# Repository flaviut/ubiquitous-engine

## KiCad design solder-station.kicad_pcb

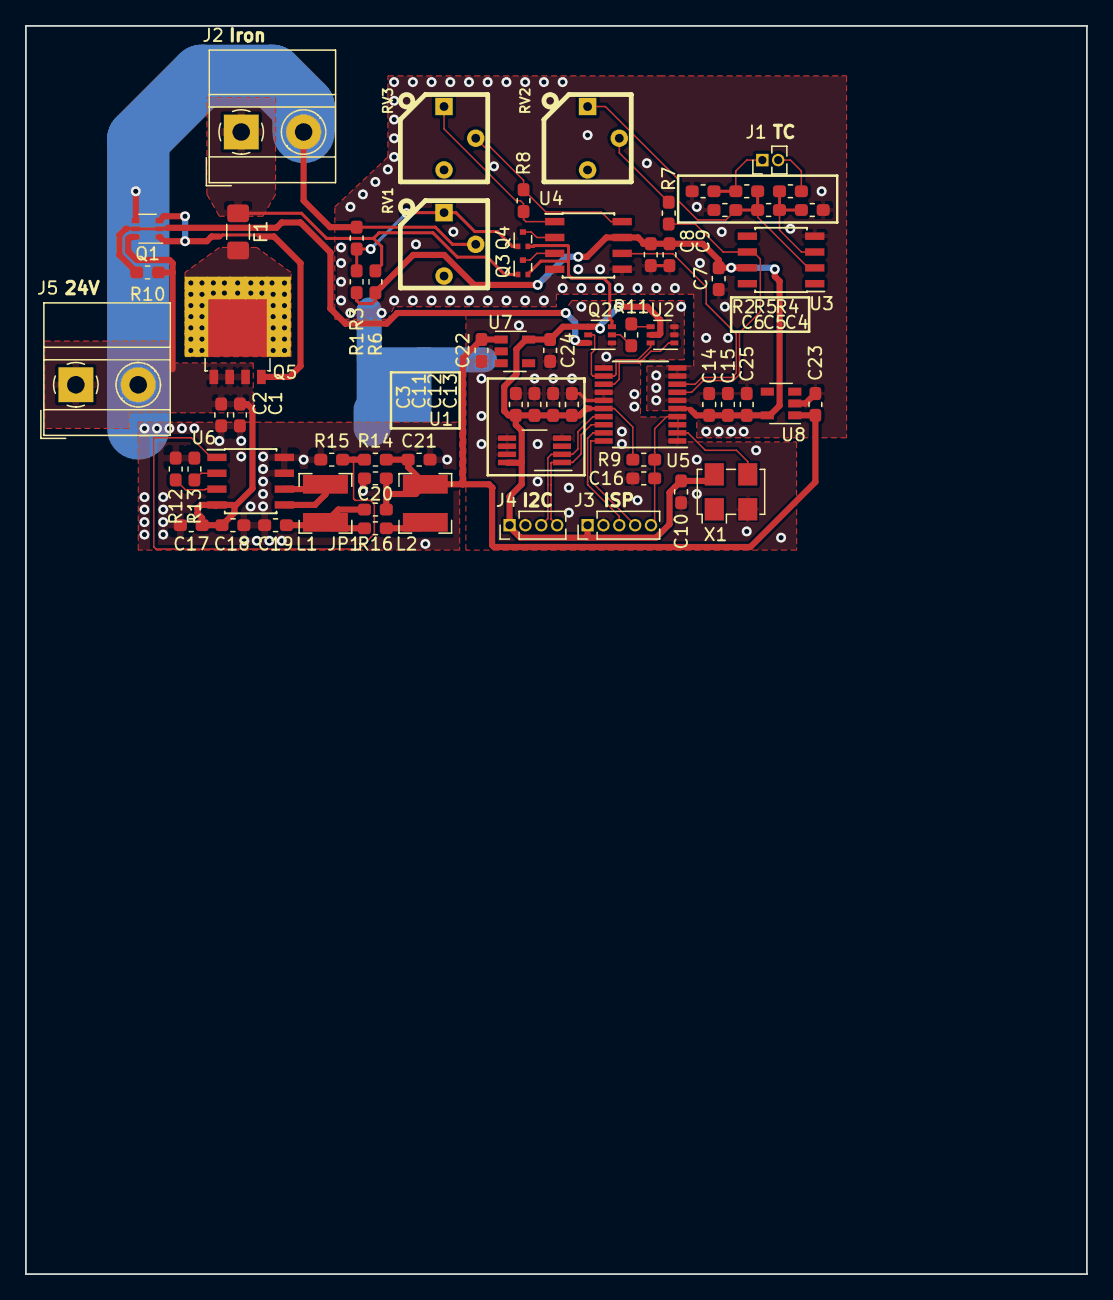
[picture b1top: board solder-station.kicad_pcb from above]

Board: 2 copper layers, 85.0 x 100.0 mm, 68 parts (1 on the bottom side), 40 nets.

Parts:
C1, C10, C11: 4.7u; C_0603_1608Metric_Pad1.05x0.95mm_HandSolder
C2, C7, C8, C12, C13, C14, C16: .1u; C_0603_1608Metric_Pad1.05x0.95mm_HandSolder
C3, C9, C15, C22, C23, C24, C25: 1u; C_0603_1608Metric_Pad1.05x0.95mm_HandSolder
C4, C6: 1n; C_0603_1608Metric_Pad1.05x0.95mm_HandSolder
C5: 10n; C_0603_1608Metric_Pad1.05x0.95mm_HandSolder
C17, C18, C19, C20, C21: 47u; C_0603_1608Metric_Pad1.05x0.95mm_HandSolder
F1: 10A; Fuse_1206_3216Metric_Pad1.42x1.75mm_HandSolder
J1: Temp Sensor; PinHeader_1x02_P1.27mm_Vertical
J2: Heating Element; TerminalBlock_MetzConnect_Type011_RT05502HBWC_1x02_P5.00mm_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
J3: ISP; PinHeader_1x05_P1.27mm_Vertical
J4: I2C; PinHeader_1x04_P1.27mm_Vertical
J5: Power; TerminalBlock_MetzConnect_Type011_RT05502HBWC_1x02_P5.00mm_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
JP1: SolderJumper_2_Open; R_0603_1608Metric_Pad1.05x0.95mm_HandSolder
L1, L2: 4.7u; L_Bourns-SRN4018
NT1: Star Ground; NetTie-4_SMD_Pad2.0mm
Q1, Q2: MBT3946DW1T1; SOT-363_SC-70-6
Q3, Q4: L2N7002M3T5G; SOT-723
Q5: FDMS6681Z; LFPAK56_ThermalVias-1
R1, R6: 2k 0.1%; R_0603_1608Metric_Pad1.05x0.95mm_HandSolder
R2, R7: 1M; R_0603_1608Metric_Pad1.05x0.95mm_HandSolder
R3: 3.3; R_0603_1608Metric_Pad1.05x0.95mm_HandSolder
R4, R5, R10: 10k; R_0603_1608Metric_Pad1.05x0.95mm_HandSolder
R8: DNP; R_0603_1608Metric_Pad1.05x0.95mm_HandSolder
R9: 100k; R_0603_1608Metric_Pad1.05x0.95mm_HandSolder
R11: 0; R_0603_1608Metric_Pad1.05x0.95mm_HandSolder
R12: 27k; R_0603_1608Metric_Pad1.05x0.95mm_HandSolder
R13: 120k; R_0603_1608Metric_Pad1.05x0.95mm_HandSolder
R14: 475k; R_0603_1608Metric_Pad1.05x0.95mm_HandSolder
R15: 150k; R_0603_1608Metric_Pad1.05x0.95mm_HandSolder
R16: 150m; R_0603_1608Metric_Pad1.05x0.95mm_HandSolder
RV1: 3362P-1-100; BOURNS-3362P_pot
RV2: 3362P-1-105; BOURNS-3362P_pot
RV3: 3362P-1-502; BOURNS-3362P_pot
U1: LM75B; VSSOP-8_3.0x3.0mm_P0.65mm
U2: 74LVC1G57; SOT-363_SC-70-6
U3: OPA333xxD; SOIC-8_3.9x4.9mm_P1.27mm
U4: INA126; SOIC-8_3.9x4.9mm_P1.27mm
U5: STM32F030F4Px; TSSOP-20_4.4x6.5mm_P0.65mm
U6: FM1613; SOIC-8_3.9x4.9mm_P1.27mm
U7, U8: XC6201P332; SOT-23-5
X1: 20MHz; Oscillator_SMD_EuroQuartz_XO53-4Pin_5.0x3.2mm_HandSoldering

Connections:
+3.3VA: C7.2, C8.1, C9.1, C14.1, C15.1, C25.1, R1.1, R6.1, U3.7, U4.7, U5.5, U8.5
+3V3: C3.1, C10.1, C11.1, C12.1, C13.1, C24.1, J3.1, J4.1, Q2.4, R9.1, U1.8, U2.5, U5.16, U7.5, X1.4
+5V: C20.1, C21.1, C22.1, C23.1, JP1.2, L2.1, R14.2, U7.1, U8.1
+24V: C1.1, C2.1, C17.1, C18.1, J5.1, Q1.6, Q5.1, Q5.2, Q5.3, R10.1, U6.4
/A_IRON: U4.6, U5.8
/A_THERMO: R7.1, U3.6, U5.7
/EN_PWR: U2.1, U5.13
/EN_SEN: Q2.5, U2.6, U5.12
/I2C1_SCL: J4.3, U1.2, U5.17
/I2C1_SDA: J4.4, U1.1, U5.18
/IRON_PWR: F1.1, J2.1, Q3.1, R6.2
/I_RESET: C16.1, J3.5, R9.2, U5.4
/I_SWCLK: J3.4, U5.20
/I_SWDIO: J3.3, U5.19
GND: C1.2, C2.2, C17.2, C18.2, C19.2, C20.2, C21.2, J2.2, J5.2, NT1.4, Q1.4, R3.2, R12.2, R13.2, R15.2, RV1.2, U6.7, U6.8
GNDA: C4.1, C6.2, C7.1, C8.2, C9.2, C14.2, C15.2, C23.2, C25.2, NT1.2, R2.2, U3.4, U4.4, U4.5, U5.6, U5.9, U5.10, U8.2
GNDD: C3.2, C10.2, C11.2, C12.2, C13.2, C16.2, C22.2, C24.2, J3.2, J4.2, NT1.1, Q2.1, U1.4, U1.5, U1.6, U1.7, U2.2, U2.3, U5.1, U5.11, U5.14, U5.15, U7.2, X1.2
unnamed: C4.2, C5.1, R4.1, U3.3
unnamed: C5.2, C6.1, R5.2, RV2.1, U3.2
unnamed: C19.1, JP1.1, L1.1, R16.2
unnamed: F1.2, Q5.5
unnamed: J1.1, R2.1, R5.1
unnamed: J1.2, R4.2
unnamed: L1.2, U6.5, U6.6
unnamed: L2.2, R16.1
unnamed: Q1.1, Q1.3, Q5.4
unnamed: Q1.2, Q1.5, Q2.6, R10.2
unnamed: Q2.2, R11.1
unnamed: Q2.3, Q3.2, Q4.2
unnamed: Q3.3, U4.3
unnamed: Q4.1, R1.2, R3.1, RV1.1
unnamed: Q4.3, U4.2
unnamed: R7.2, RV2.2
unnamed: R8.1, RV3.1, U4.1
unnamed: R8.2, RV3.2, U4.8
unnamed: R11.2, U2.4
unnamed: R12.1, U6.3
unnamed: R13.1, U6.2
unnamed: R14.1, R15.1, U6.1
unnamed: U5.2, X1.3

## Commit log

2019-01-29 Remove solder mask from mosfet heatsink
2019-01-29 Fix DRC issues
2019-01-29 Fix bug where mosfet would not work & reduce cm^2
2019-02-02 Add beginnings of a PSU & power filtering
2019-02-04 Add power supplies
2019-02-06 Move some things around
2019-02-06 Add test points
2019-04-30 Add block diagram
2019-05-07 Add initial skidl
2019-05-07 Add more sims
2019-05-07 Misc changes
2019-05-08 Add resistive divider
